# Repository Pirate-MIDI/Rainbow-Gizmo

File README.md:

# Rainbow-Gizmo
Open source MIDI to addressable RGB adapter for musicians and makers

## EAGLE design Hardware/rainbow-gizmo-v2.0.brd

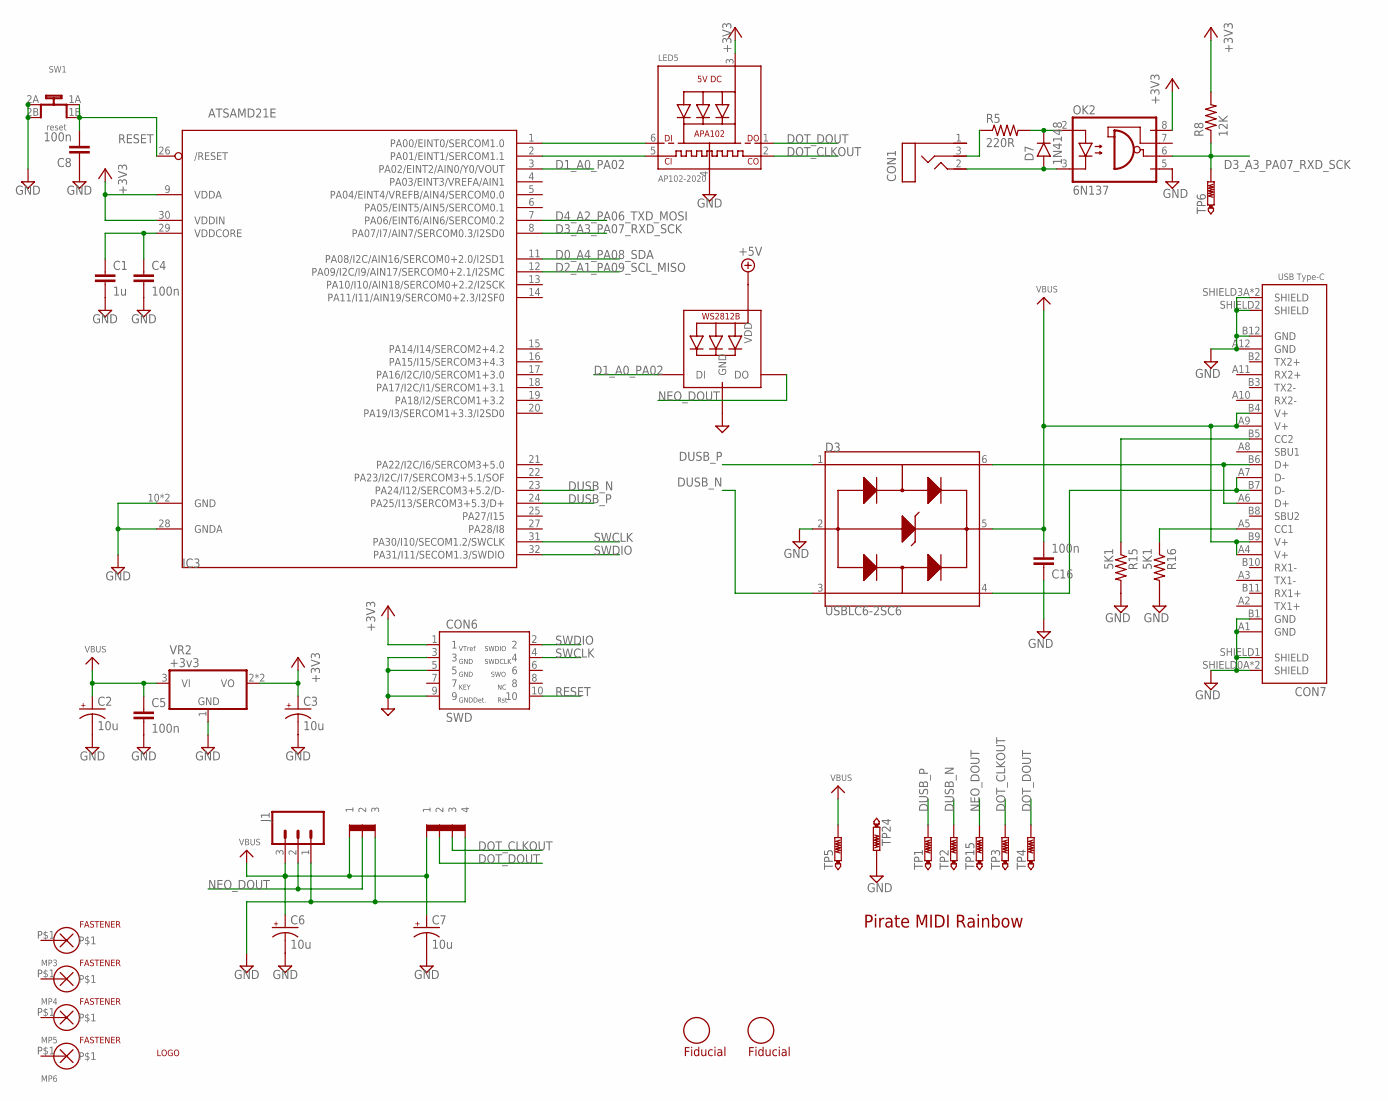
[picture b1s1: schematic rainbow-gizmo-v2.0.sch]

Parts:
C1: 1u; 0603_CAP
C2, C3, C6, C7: 10u; PANASONIC_B
C4, C5, C8, C16: 100n; 0603_CAP
CON1: TRS3.5MM; SJ-352*-SMT
CON2: 1X3PADS; 1X3_PADS
CON4: 1X4; 1X4_PADS
CON6: SWD; 5X2_1.27MM_SMD
CON7: DUAL SMT; 10137064-00021LF
D3: USBLC6-2SC6; SOT95P280X145-6N
D7: 1N4148; SOD-323
FD3: FIDUCIALSQUARE_1MM; FIDUCIAL_SQUARE_1MM
FD4: FIDUCIALROUND_1MM; FIDUCIAL_ROUND_1MM
IC3: ATSAMD21E; QFN32_5MM
J1: 1X3PH; JST_S3B-PH-SM4-TB
LED1: WS2812B2020; LED2020RGB
LED5: AP102-2020; APA102_2020
MP3, MP4, MP5, MP6: SCREW-FASTENER2.5; M2.5-PANHEAD-VIA
OK2: 6N137; SMD8
R5: 220R; 0603-RES
R8: 12K; 0603-RES
R15, R16: 5K1; 0603-RES
SW1: reset; KMR_X
TP1, TP2, TP3, TP4, TP5, TP6, TP15, TP24: PTR1B1,27; B1,27
U$5: PM_LOGOSSTOP_M; PM_M_MAIN_LOGO1_STOP
VR2: +3v3; SOT223

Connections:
+3V3: C3.+, CON6.1, IC3.9 (VDDA), IC3.30 (VDDIN), LED5.3 (VDD), OK2.8 (VCC), R8.2, VR2.2 (VO), VR2.4 (VO)
+5V: LED1.4 (VDD)
A3: IC3.1 (PA00/EINT0/SERCOM1.0), LED5.6 (DI)
CC1: CON7.A5 (CC1), R16.1
CC2: CON7.B5 (CC2), R15.1
D0_A4_PA08_SDA: IC3.11 (PA08/I2C/AIN16/SERCOM0+2.0/I2SD1)
D1_A0_PA02: IC3.3 (PA02/EINT2/AIN0/Y0/VOUT), LED1.3 (DI)
D2_A1_PA09_SCL_MISO: IC3.12 (PA09/I2C/I9/AIN17/SERCOM0+2.1/I2SMC)
D3_A3_PA07_RXD_SCK: IC3.8 (PA07/I7/AIN7/SERCOM0.3/I2SD0), OK2.6 (VO), R8.1, TP6.TP
D4_A2_PA06_TXD_MOSI: IC3.7 (PA06/EINT6/AIN6/SERCOM0.2)
DOT_CLKOUT: CON4.P$3 (3), LED5.2 (CKO), TP3.TP
DOT_DOUT: CON4.P$2 (2), LED5.1 (DO), TP4.TP
DUSB_N: D3.3 (I/O2), IC3.23 (PA24/I12/SERCOM3+5.2/D-), TP2.TP
DUSB_P: D3.1 (I/O1), IC3.24 (PA25/I13/SERCOM3+5.3/D+), TP1.TP
GND: C1.2, C2.-, C3.-, C4.2, C5.2, C6.-, C7.-, C8.1, C16.1, CON2.P$3 (3), CON4.P$4 (4), CON6.3, CON6.5, CON6.9, CON7.A1 (GND), CON7.A12 (GND), CON7.B1 (GND), CON7.B12 (GND), CON7.SHIELD0A (SHIELD), CON7.SHIELD0B (SHIELD), CON7.SHIELD1 (SHIELD), CON7.SHIELD2 (SHIELD), CON7.SHIELD3A (SHIELD), CON7.SHIELD3B (SHIELD), D3.2 (GND), IC3.10 (GND), IC3.28 (GNDA), IC3.33 (GND), J1.1, LED1.2 (GND), LED5.4 (GND), OK2.5 (GND), R15.2, R16.2, SW1.2A (3), SW1.2B (4), TP24.TP, VR2.1 (GND)
unnamed: CON1.2 (T), D7.A, OK2.3 (C)
unnamed: IC3.2 (PA01/EINT1/SERCOM1.1), LED5.5 (CKI)
unnamed: D7.C, OK2.2 (A), R5.2
unnamed: CON1.3 (R), R5.1
unnamed: CON7.A6 (D+), CON7.B6 (D+), D3.6 (I/O3)
unnamed: CON7.A7 (D-), CON7.B7 (D-), D3.4 (I/O4)
NEO_DOUT: CON2.P$2 (2), J1.2, LED1.1 (DO), TP15.TP
RESET: C8.2, CON6.10, IC3.26 (/RESET), SW1.1A (1), SW1.1B (2)
SWCLK: CON6.4, IC3.31 (PA30/I10/SECOM1.2/SWCLK)
SWDIO: CON6.2, IC3.32 (PA31/I11/SECOM1.3/SWDIO)
VBUS: C2.+, C5.1, C6.+, C7.+, C16.2, CON2.P$1 (1), CON4.P$1 (1), CON7.A4 (V+), CON7.A9 (V+), CON7.B4 (V+), CON7.B9 (V+), D3.5 (VBUS), J1.3, TP5.TP, VR2.3 (VI)
VDDCORE1: C1.1, C4.1, IC3.29 (VDDCORE)

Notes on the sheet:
Pirate MIDI Rainbow

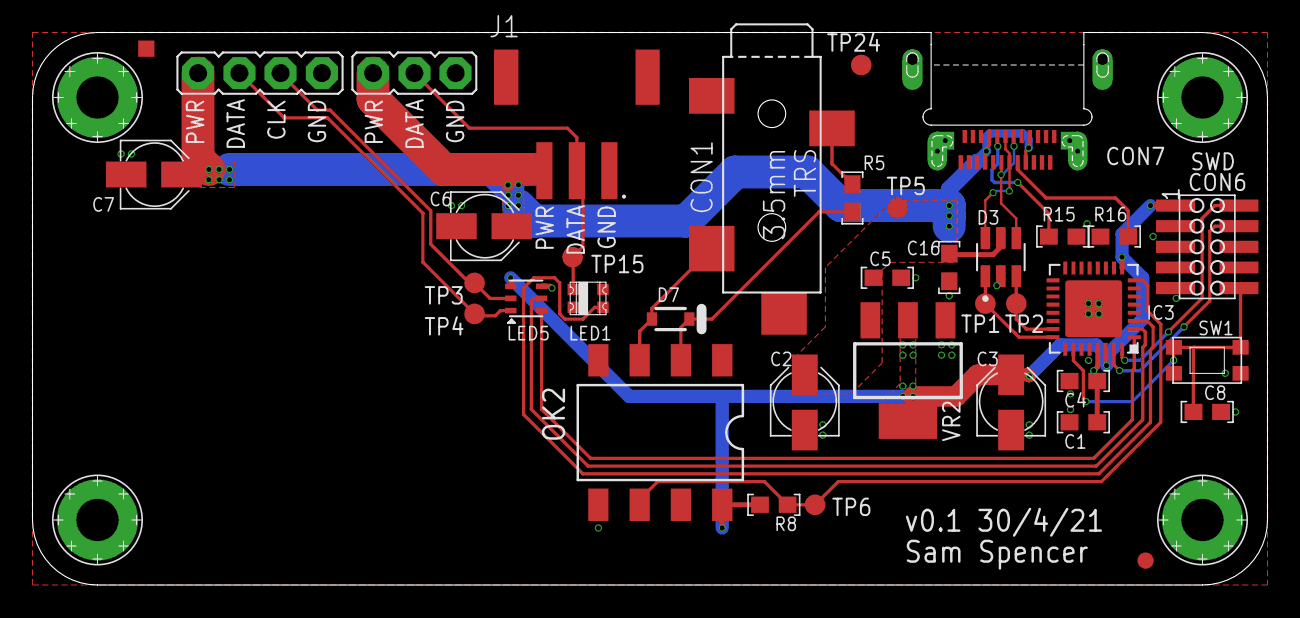
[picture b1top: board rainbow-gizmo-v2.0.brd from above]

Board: 2 copper layers, 76.0 x 34.0 mm, 42 parts (0 on the bottom side), 23 nets.

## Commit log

2021-04-30 Added v2.0 hardware design files

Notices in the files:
parts and their libraries:
microbuilder: This work is placed in the public domain, and may be freely used for commercial and non-commercial work with the following conditions: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
